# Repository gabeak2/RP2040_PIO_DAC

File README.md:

https://www.youtube.com/watch?v=1zT0gdcFlgw

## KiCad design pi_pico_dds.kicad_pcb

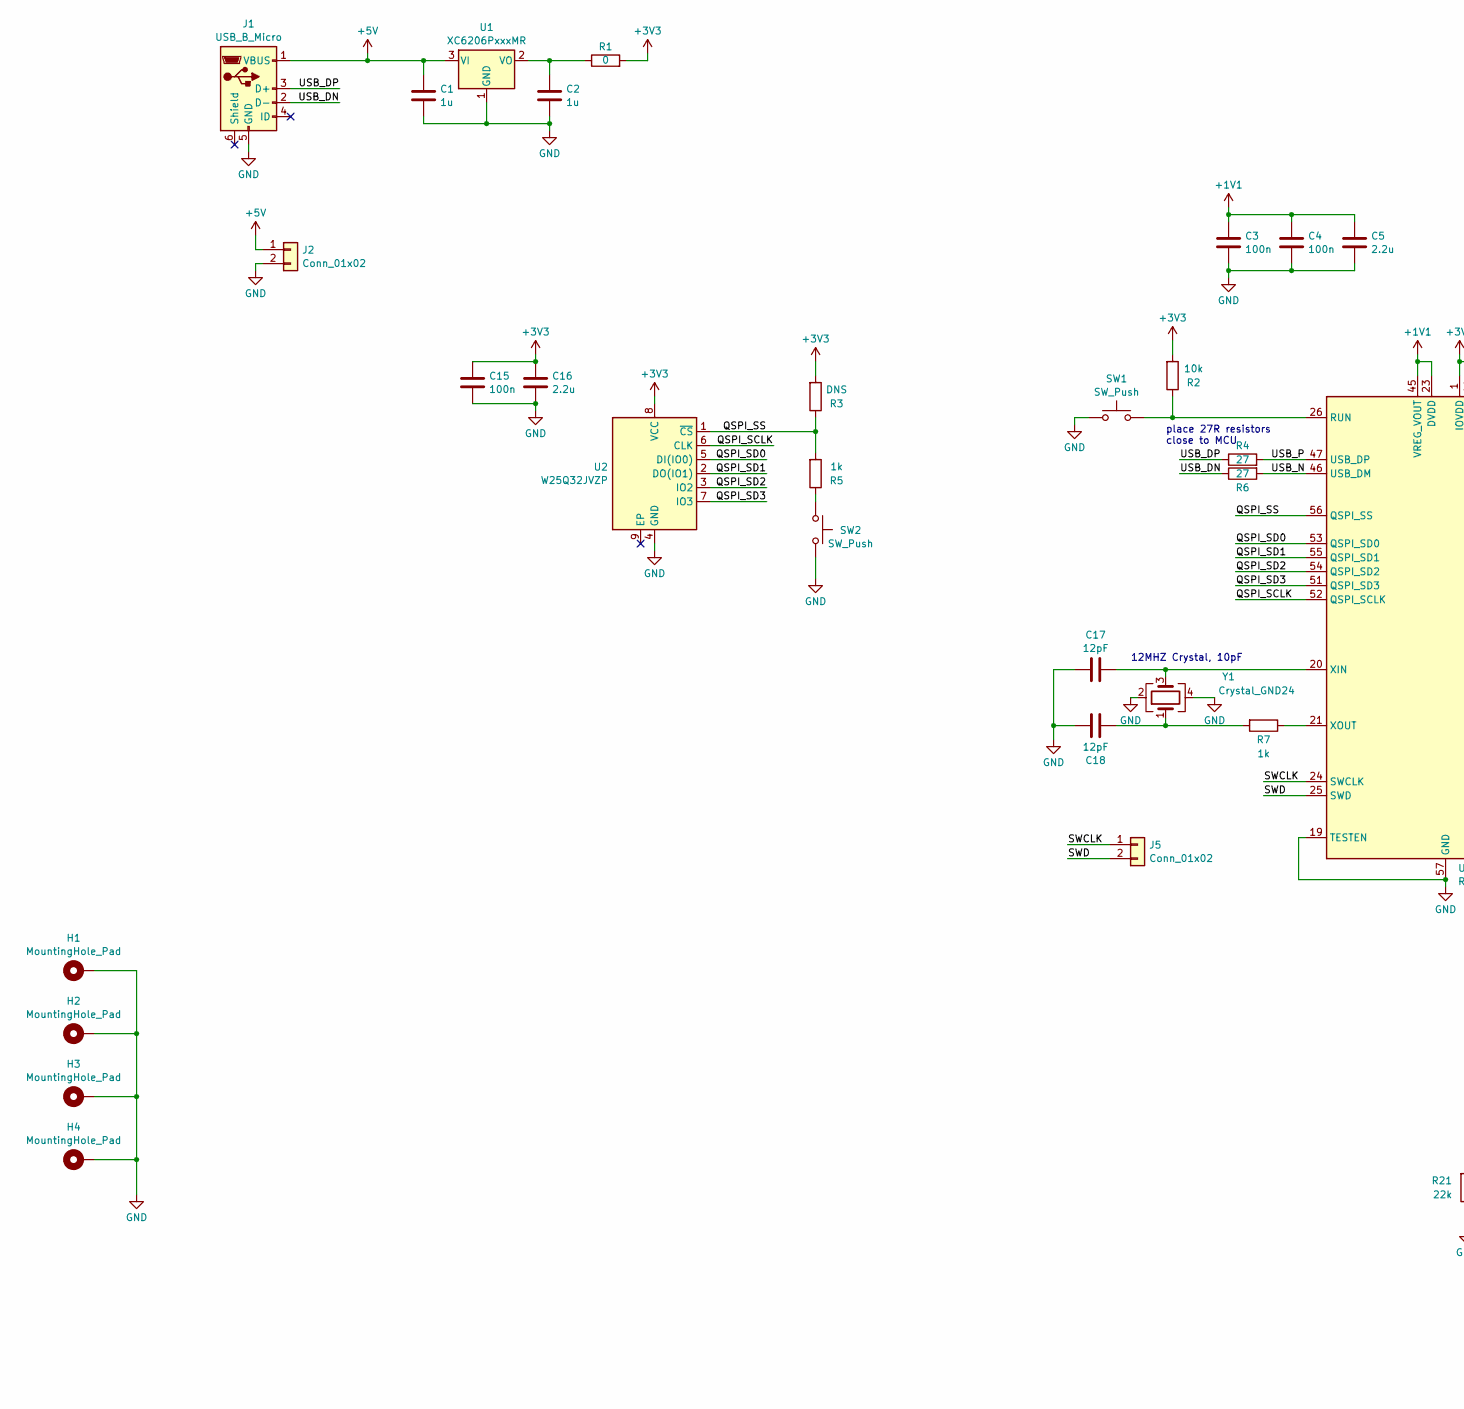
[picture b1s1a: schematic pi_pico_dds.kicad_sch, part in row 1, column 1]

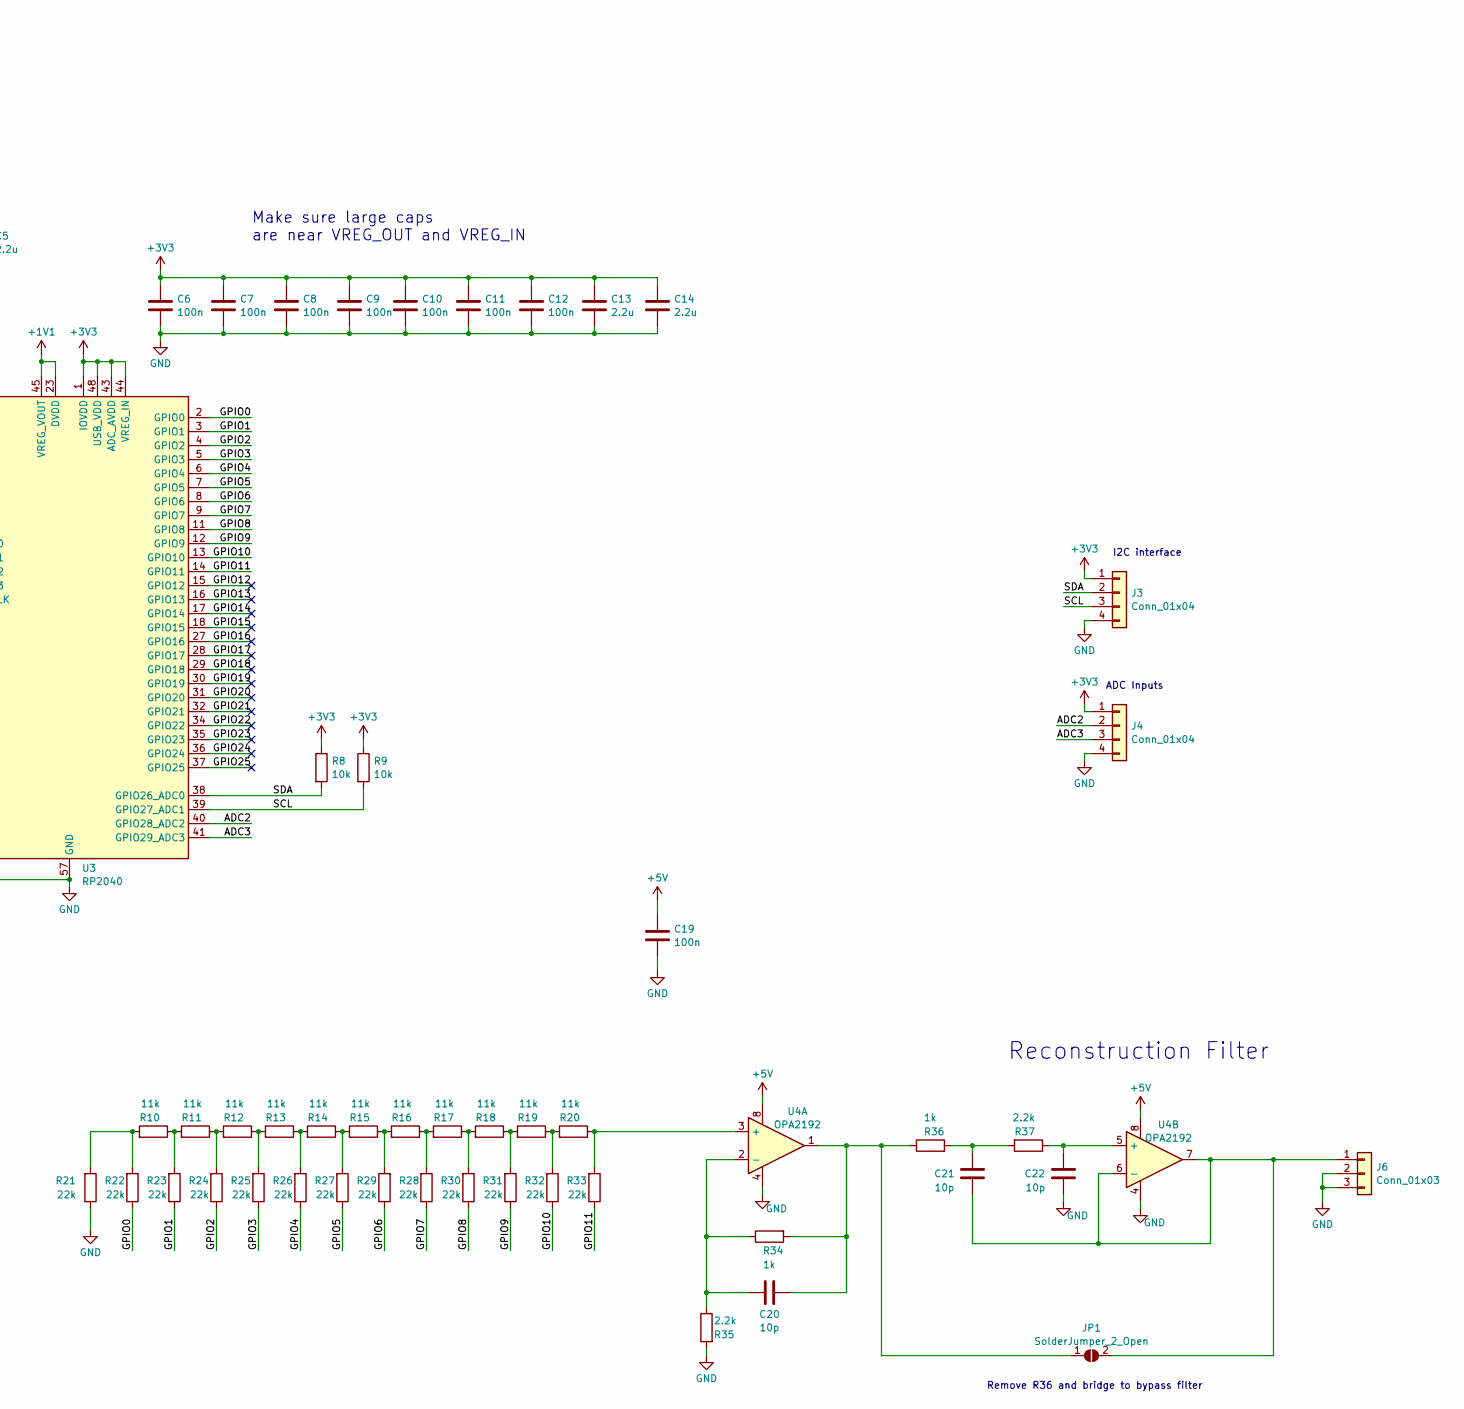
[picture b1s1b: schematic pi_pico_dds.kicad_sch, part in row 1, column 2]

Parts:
C1, C2: 1u; C_0402_1005Metric; LCSC C52923
C3, C4, C6, C7, C8, C9, C10, C11, C12, C15, C19: 100n; C_0402_1005Metric; LCSC C307331
C5, C13, C14, C16: 2.2u; C_0402_1005Metric; LCSC C12530
C17, C18: 12pF; C_0402_1005Metric; LCSC C1547
C20, C21, C22: 10p; C_0402_1005Metric; LCSC C32949
H1, H2, H3, H4: MountingHole_Pad; MountingHole_2.2mm_M2_DIN965_Pad
J1: USB_B_Micro; USB_Micro-B_Molex-105017-0001; LCSC C505111
J2, J5: Conn_01x02; PinSocket_1x02_P2.54mm_Vertical
J3, J4: Conn_01x04; PinSocket_1x04_P2.54mm_Vertical
J6: Conn_01x03; PinSocket_1x03_P2.54mm_Vertical
JP1: SolderJumper_2_Open; SolderJumper-2_P1.3mm_Open_Pad1.0x1.5mm
R1: 0; R_0402_1005Metric; LCSC C17168
R2, R8, R9: 10k; R_0402_1005Metric; LCSC C25744
R3: DNS; R_0402_1005Metric
R4, R6: 27; R_0402_1005Metric; LCSC C25100
R5, R7, R34, R36: 1k; R_0402_1005Metric; LCSC C11702
R10, R11, R12, R13, R14, R15, R16, R17, R18, R19, R20: 11k; R_0402_1005Metric; LCSC C705064
R21, R22, R23, R24, R25, R26, R27, R28, R29, R30, R31, R32, R33: 22k; R_0402_1005Metric; LCSC C326601
R35, R37: 2.2k; R_0402_1005Metric; LCSC C25879
SW1, SW2: SW_Push; SW_Push_1P1T_XKB_TS-1187A
U1: XC6206PxxxMR; SOT-23-3; LCSC C5446
U2: W25Q32JVZP; WSON-8-1EP_6x5mm_P1.27mm_EP3.4x4.3mm; LCSC C571260
U3: RP2040; QFN-56-1EP_7x7mm_P0.4mm_EP3.2x3.2mm; LCSC C2040
U4: OPA2192; SOIC-8_3.9x4.9mm_P1.27mm; LCSC C110074
Y1: Crystal_GND24; Crystal_SMD_3225-4Pin_3.2x2.5mm; LCSC C50430

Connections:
+1V1: C3.1, C4.1, C5.1, U3.23 (DVDD), U3.45 (VREG_VOUT), U3.50 (DVDD)
+3V3: C6.1, C7.1, C8.1, C9.1, C10.1, C11.1, C12.1, C13.1, C14.1, C15.1, C16.1, J3.1, J4.1, R1.2, R2.2, R3.2, R8.1, R9.1, U2.8 (VCC), U3.1 (IOVDD), U3.10 (IOVDD), U3.22 (IOVDD), U3.33 (IOVDD), U3.42 (IOVDD), U3.43 (ADC_AVDD), U3.44 (VREG_IN), U3.48 (USB_VDD), U3.49 (IOVDD)
+5V: C1.1, C19.1, J1.1 (VBUS), J2.1, U1.3 (VI), U4.8
/ADC2: J4.2, U3.40 (GPIO28_ADC2)
/ADC3: J4.3, U3.41 (GPIO29_ADC3)
/GPIO0: R22.1, U3.2 (GPIO0)
/GPIO1: R23.1, U3.3 (GPIO1)
/GPIO2: R24.1, U3.4 (GPIO2)
/GPIO3: R25.1, U3.5 (GPIO3)
/GPIO4: R26.1, U3.6 (GPIO4)
/GPIO5: R27.1, U3.7 (GPIO5)
/GPIO6: R28.1, U3.8 (GPIO6)
/GPIO7: R29.1, U3.9 (GPIO7)
/GPIO8: R30.1, U3.11 (GPIO8)
/GPIO9: R31.1, U3.12 (GPIO9)
/GPIO10: R32.1, U3.13 (GPIO10)
/GPIO11: R33.1, U3.14 (GPIO11)
/GPIO12: U3.15 (GPIO12)
/GPIO13: U3.16 (GPIO13)
/GPIO14: U3.17 (GPIO14)
/GPIO15: U3.18 (GPIO15)
/GPIO16: U3.27 (GPIO16)
/GPIO17: U3.28 (GPIO17)
/GPIO18: U3.29 (GPIO18)
/GPIO19: U3.30 (GPIO19)
/GPIO20: U3.31 (GPIO20)
/GPIO21: U3.32 (GPIO21)
/GPIO22: U3.34 (GPIO22)
/GPIO23: U3.35 (GPIO23)
/GPIO24: U3.36 (GPIO24)
/GPIO25: U3.37 (GPIO25)
/QSPI_SCLK: U2.6 (CLK), U3.52 (QSPI_SCLK)
/QSPI_SD0: U2.5 (DI(IO0)), U3.53 (QSPI_SD0)
/QSPI_SD1: U2.2 (DO(IO1)), U3.55 (QSPI_SD1)
/QSPI_SD2: U2.3 (IO2), U3.54 (QSPI_SD2)
/QSPI_SD3: U2.7 (IO3), U3.51 (QSPI_SD3)
/QSPI_SS: R3.1, R5.2, U2.1 (~CS), U3.56 (QSPI_SS)
/SCL: J3.3, R9.2, U3.39 (GPIO27_ADC1)
/SDA: J3.2, R8.2, U3.38 (GPIO26_ADC0)
/SWCLK: J5.1, U3.24 (SWCLK)
/SWD: J5.2, U3.25 (SWD)
/USB_DN: J1.2 (D-), R6.1
/USB_DP: J1.3 (D+), R4.1
/USB_N: R6.2, U3.46 (USB_DM)
/USB_P: R4.2, U3.47 (USB_DP)
GND: C1.2, C2.2, C3.2, C4.2, C5.2, C6.2, C7.2, C8.2, C9.2, C10.2, C11.2, C12.2, C13.2, C14.2, C15.2, C16.2, C17.1, C18.1, C19.2, C22.2, H1.1, H2.1, H3.1, H4.1, J1.5 (GND), J2.2, J3.4, J4.4, J6.2, J6.3, R21.1, R35.2, SW1.1, SW2.1, U1.1 (GND), U2.4 (GND), U3.19 (TESTEN), U3.57 (GND), U4.4, Y1.2, Y1.4
unnamed: C18.2, R7.2, Y1.1
unnamed: C21.1, R36.2, R37.2
unnamed: C21.2, J6.1, JP1.2 (B), U4.6 (-), U4.7
unnamed: C20.1, JP1.1 (A), R34.2, R36.1, U4.1
unnamed: R5.1, SW2.2
unnamed: R10.1, R11.2, R23.2
unnamed: R10.2, R21.2, R22.2
unnamed: R11.1, R12.2, R24.2
unnamed: R12.1, R13.2, R25.2
unnamed: R13.1, R14.2, R26.2
unnamed: R14.1, R15.2, R27.2
unnamed: R15.1, R16.2, R28.2
unnamed: R16.1, R17.2, R29.2
unnamed: R17.1, R18.2, R30.2
unnamed: R18.1, R19.2, R31.2
unnamed: R19.1, R20.2, R32.2
unnamed: C2.1, R1.1, U1.2 (VO)
unnamed: R2.1, SW1.2, U3.26 (RUN)
unnamed: C17.2, U3.20 (XIN), Y1.3
unnamed: R7.1, U3.21 (XOUT)
unnamed: R20.1, R33.2, U4.3 (+)
unnamed: C20.2, R34.1, R35.1, U4.2 (-)
unnamed: C22.1, R37.1, U4.5 (+)

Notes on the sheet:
ADC Inputs
I2C interface
place 27R resistors close to MCU
Remove R36 and bridge to bypass filter
Reconstruction Filter
Make sure large caps are near VREG_OUT and VREG_IN
12MHZ Crystal, 10pF

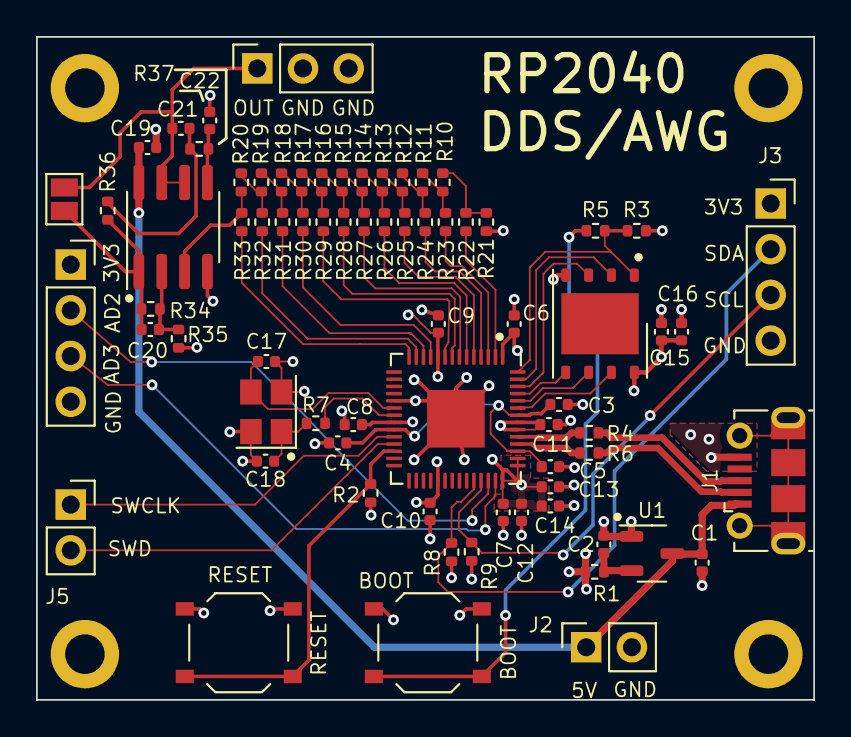
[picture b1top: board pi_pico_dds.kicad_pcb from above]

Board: 4 copper layers, 43.2 x 36.8 mm, 77 parts (0 on the bottom side), 55 nets.

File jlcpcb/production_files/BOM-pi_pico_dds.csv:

Comment,Designator,Footprint,LCSC
OPA2192,U4,SOIC-8_3.9x4.9mm_P1.27mm,C110074
1k,"R34,R36,R5,R7",R_0402_1005Metric,C11702
2.2u,"C13,C14,C16,C5",C_0402_1005Metric,C12530
12pF,"C17,C18",C_0402_1005Metric,C1547
0,R1,R_0402_1005Metric,C17168
RP2040,U3,QFN-56-1EP_7x7mm_P0.4mm_EP3.2x3.2mm,C2040
27,"R4,R6",R_0402_1005Metric,C25100
10k,"R2,R8,R9",R_0402_1005Metric,C25744
2.2k,"R35,R37",R_0402_1005Metric,C25879
100n,"C10,C11,C12,C15,C19,C3,C4,C6,C7,C8,C9",C_0402_1005Metric,C307331
SW_Push,"SW1,SW2",SW_Push_1P1T_XKB_TS-1187A,C318884
22k,"R21,R22,R23,R24,R25,R26,R27,R28,R29,R30,R31,R32,R33",R_0402_1005Metric,C326601
10p,"C20,C21,C22",C_0402_1005Metric,C32949
Crystal_GND24,Y1,Crystal_SMD_3225-4Pin_3.2x2.5mm,C50430
USB_B_Micro,J1,USB_Micro-B_Molex-105017-0001,C505111
1u,"C1,C2",C_0402_1005Metric,C52923
XC6206PxxxMR,U1,SOT-23-3,C5446
W25Q32JVZP,U2,WSON-8-1EP_6x5mm_P1.27mm_EP3.4x4.3mm,C571260
11k,"R10,R11,R12,R13,R14,R15,R16,R17,R18,R19,R20",R_0402_1005Metric,C705064
Conn_01x04,J3,PinSocket_1x04_P2.54mm_Vertical,
Conn_01x02,J2,PinSocket_1x02_P2.54mm_Vertical,
MountingHole_Pad,H1,MountingHole_2.2mm_M2_DIN965_Pad,
MountingHole_Pad,H2,MountingHole_2.2mm_M2_DIN965_Pad,
Conn_01x04,J4,PinSocket_1x04_P2.54mm_Vertical,
MountingHole_Pad,H3,MountingHole_2.2mm_M2_DIN965_Pad,
MountingHole_Pad,H4,MountingHole_2.2mm_M2_DIN965_Pad,
Conn_01x02,J5,PinSocket_1x02_P2.54mm_Vertical,
DNS,R3,R_0402_1005Metric,
SolderJumper_2_Open,JP1,SolderJumper-2_P1.3mm_Open_Pad1.0x1.5mm,
Conn_01x03,J6,PinSocket_1x03_P2.54mm_Vertical,
